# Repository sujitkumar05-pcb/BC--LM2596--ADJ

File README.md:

# BC--LM2596--ADJ
## 1. Project Overview

The BC–LM2596–ADJ project is a DC–DC buck converter based on the LM2596 adjustable regulator, designed to efficiently step down a higher DC voltage to a stable, adjustable lower output. The circuit supports up to 3A output current and is suitable for embedded systems, power electronics, and prototyping applications. The schematic and PCB were designed using KiCad, following standard power PCB layout practices.
-----

## 2. Key Learning Objectives

Understand the working principle of a DC–DC buck (step-down) converter using the LM2596-ADJ.

Learn schematic capture, component selection, and value calculation for switching regulators.

Gain hands-on experience in power PCB layout techniques, including high-current routing, grounding, and loop minimization.

Understand the importance of input/output filtering and ripple reduction.

Apply design rule checks (DRC) and electrical rule checks (ERC) in KiCad.

Learn basic thermal considerations for power components.

Develop skills in generating manufacturing outputs such as Gerber, BOM, and pick-and-place files.
-----

## 3. Tools & Software Used
- **KiCad EDA**
  - Schematic Editor  
  - PCB Layout Editor  
  - 3D Viewer
 
 ---

## 4. Project Files
- Schematic design files (`.kicad_sch`)  
- PCB layout files (`.kicad_pcb`)  
- 3D render images  
- Manufacturing-ready Gerber files  

---

## 5. Block-Level Working Explanation

Input Power Block: Receives the DC input voltage and provides initial filtering to reduce noise and transients.

Control & Switching Block (LM2596-ADJ): Regulates the output by high-frequency switching and duty-cycle control based on feedback.

Inductor & Diode Block: Stores and transfers energy during switching cycles to achieve efficient voltage step-down.

Output Filter Block: Smooths the switching waveform using capacitors to provide a stable DC output.

Feedback Network: Uses a resistor divider to set and maintain the desired adjustable output voltage.

## 6. Bill of Materials (BOM)

| Reference | Qty | Value / Part No.    | Footprint                     |
| --------- | --- | ------------------- | ----------------------------- |
| **U1**    | 1   | LM2596S-ADJ         | TO-263-5_TabPin3              |
| **L1**    | 1   | 47 µH               | L_Bourns_SRR1208_12.7×12.7 mm |
| **D1**    | 1   | SS34 Schottky Diode | D_SMA                         |
| **D2**    | 1   | LED                 | LED_0603_1608Metric           |
| **C1**    | 1   | 100 nF              | CP_Elec_8×10                  |
| **C2**    | 1   | 100 µF              | C_0603_1608Metric             |
| **C3**    | 1   | 100 nF              | C_0603_1608Metric             |
| **C4**    | 1   | 220 µF              | CP_Elec_8×10                  |
| **R1**    | 1   | 47 kΩ               | R_0603_1608Metric             |
| **R2**    | 1   | 1 kΩ                | R_0603_1608Metric             |
| **RV1**   | 1   | 10 kΩ Potentiometer | Bourns 3296W (THT)            |
| **J1–J4** | 4   | 1×1 Pin Header      | PinHeader_1x01_P2.54 mm       |

## 7. Images & Renders

- **Schematic**

- **PCB Layout**

- **3D View**

---

## 8. Disclaimer
This project is intended for educational and reference purposes only. While the design has been tested at a basic level, it is not certified for commercial or safety-critical applications. Users are responsible for verifying the design, component ratings, and safety requirements before practical deployment.
---

## 9. Author
- **Name:** SUJIT KUMAR
- **Toolchain:** KiCad EDA

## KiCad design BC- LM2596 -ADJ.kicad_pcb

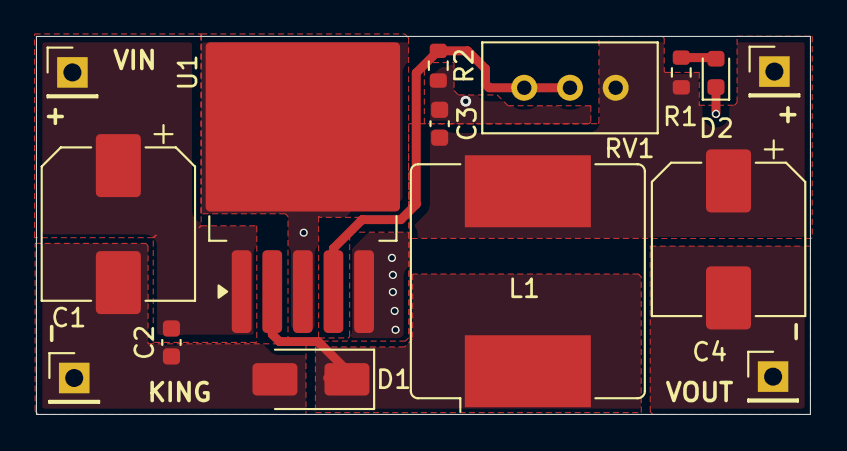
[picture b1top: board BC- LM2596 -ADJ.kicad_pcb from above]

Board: 2 copper layers, 43.0 x 21.0 mm, 15 parts (0 on the bottom side), 6 nets.

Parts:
C1: 100nF; CP_Elec_8x10
C2: 100uF; C_0603_1608Metric
C3: 100nF; C_0603_1608Metric
C4: 220uF; CP_Elec_8x10
D1: SS34; D_SMA
D2: LED; LED_0603_1608Metric
J1, J2, J3, J4: Conn_01x01_Pin; PinHeader_1x01_P2.54mm_Vertical
L1: 47uH; L_Bourns_SRR1208_12.7x12.7mm
R1: 47K; R_0603_1608Metric
R2: 1k; R_0603_1608Metric
RV1: 10K; Potentiometer_Bourns_3296W_Vertical
U1: LM2596S-ADJ; TO-263-5_TabPin3

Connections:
/VIN: C1.1, C2.1, J2.1, U1.1 (VIN)
/VOUT: C3.1, C4.1, J1.1, L1.2, R1.1, RV1.1
GND: C1.2, C2.2, C3.2, C4.2, D1.2 (A), D2.1 (K), J3.1, J4.1, R2.2, U1.3 (GND), U1.5 (~ON/OFF)
unnamed: D1.1 (K), L1.1, U1.2 (OUT)
unnamed: D2.2 (A), R1.2
unnamed: R2.1, RV1.2, RV1.3, U1.4 (FB)
